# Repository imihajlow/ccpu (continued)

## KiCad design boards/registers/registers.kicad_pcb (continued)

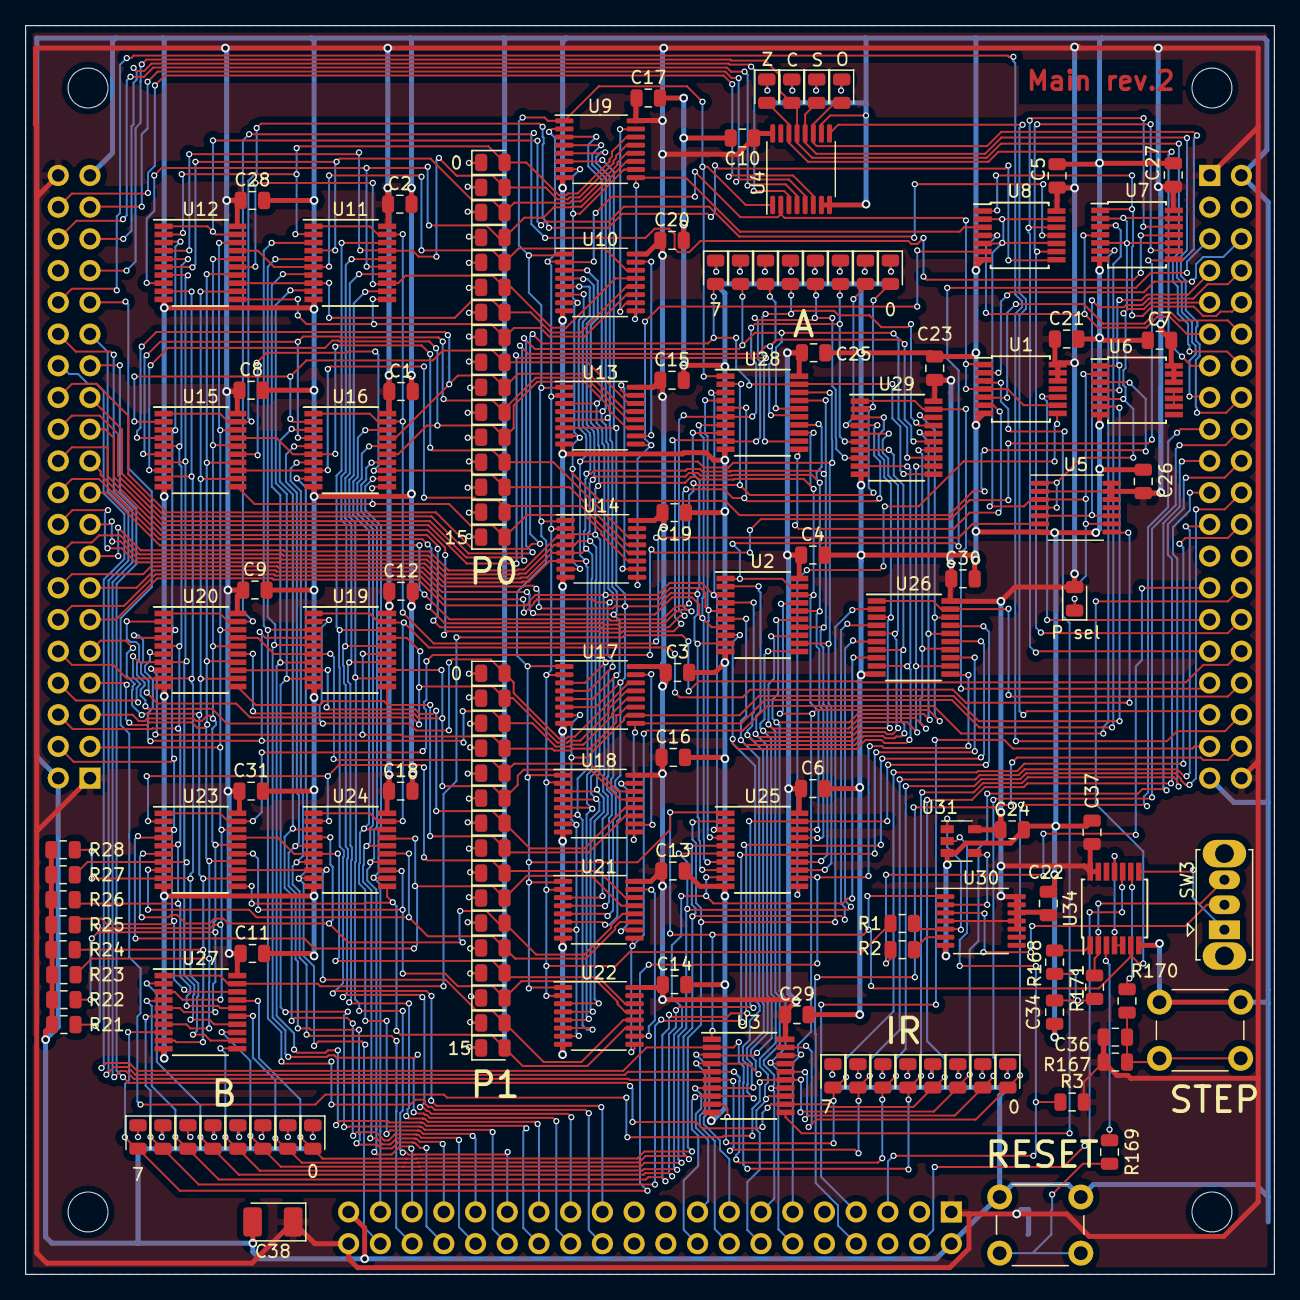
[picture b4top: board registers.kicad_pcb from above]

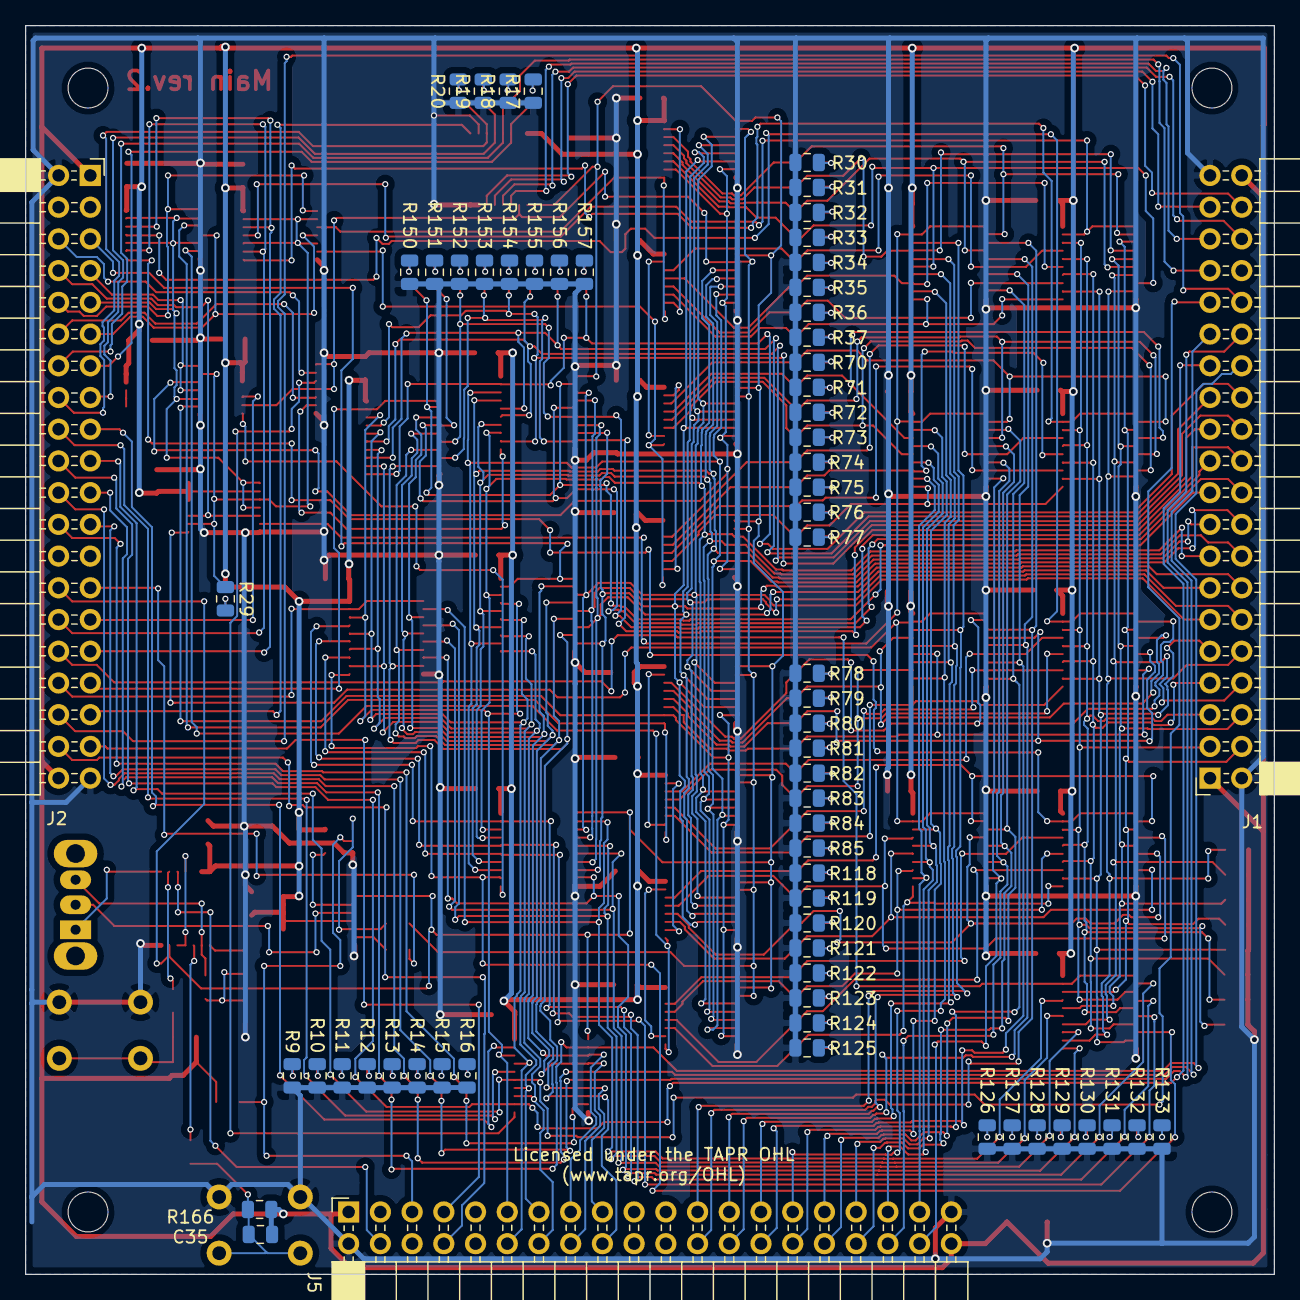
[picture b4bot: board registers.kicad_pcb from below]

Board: 2 copper layers, 100.0 x 100.0 mm, 217 parts (66 on the bottom side), 226 nets.

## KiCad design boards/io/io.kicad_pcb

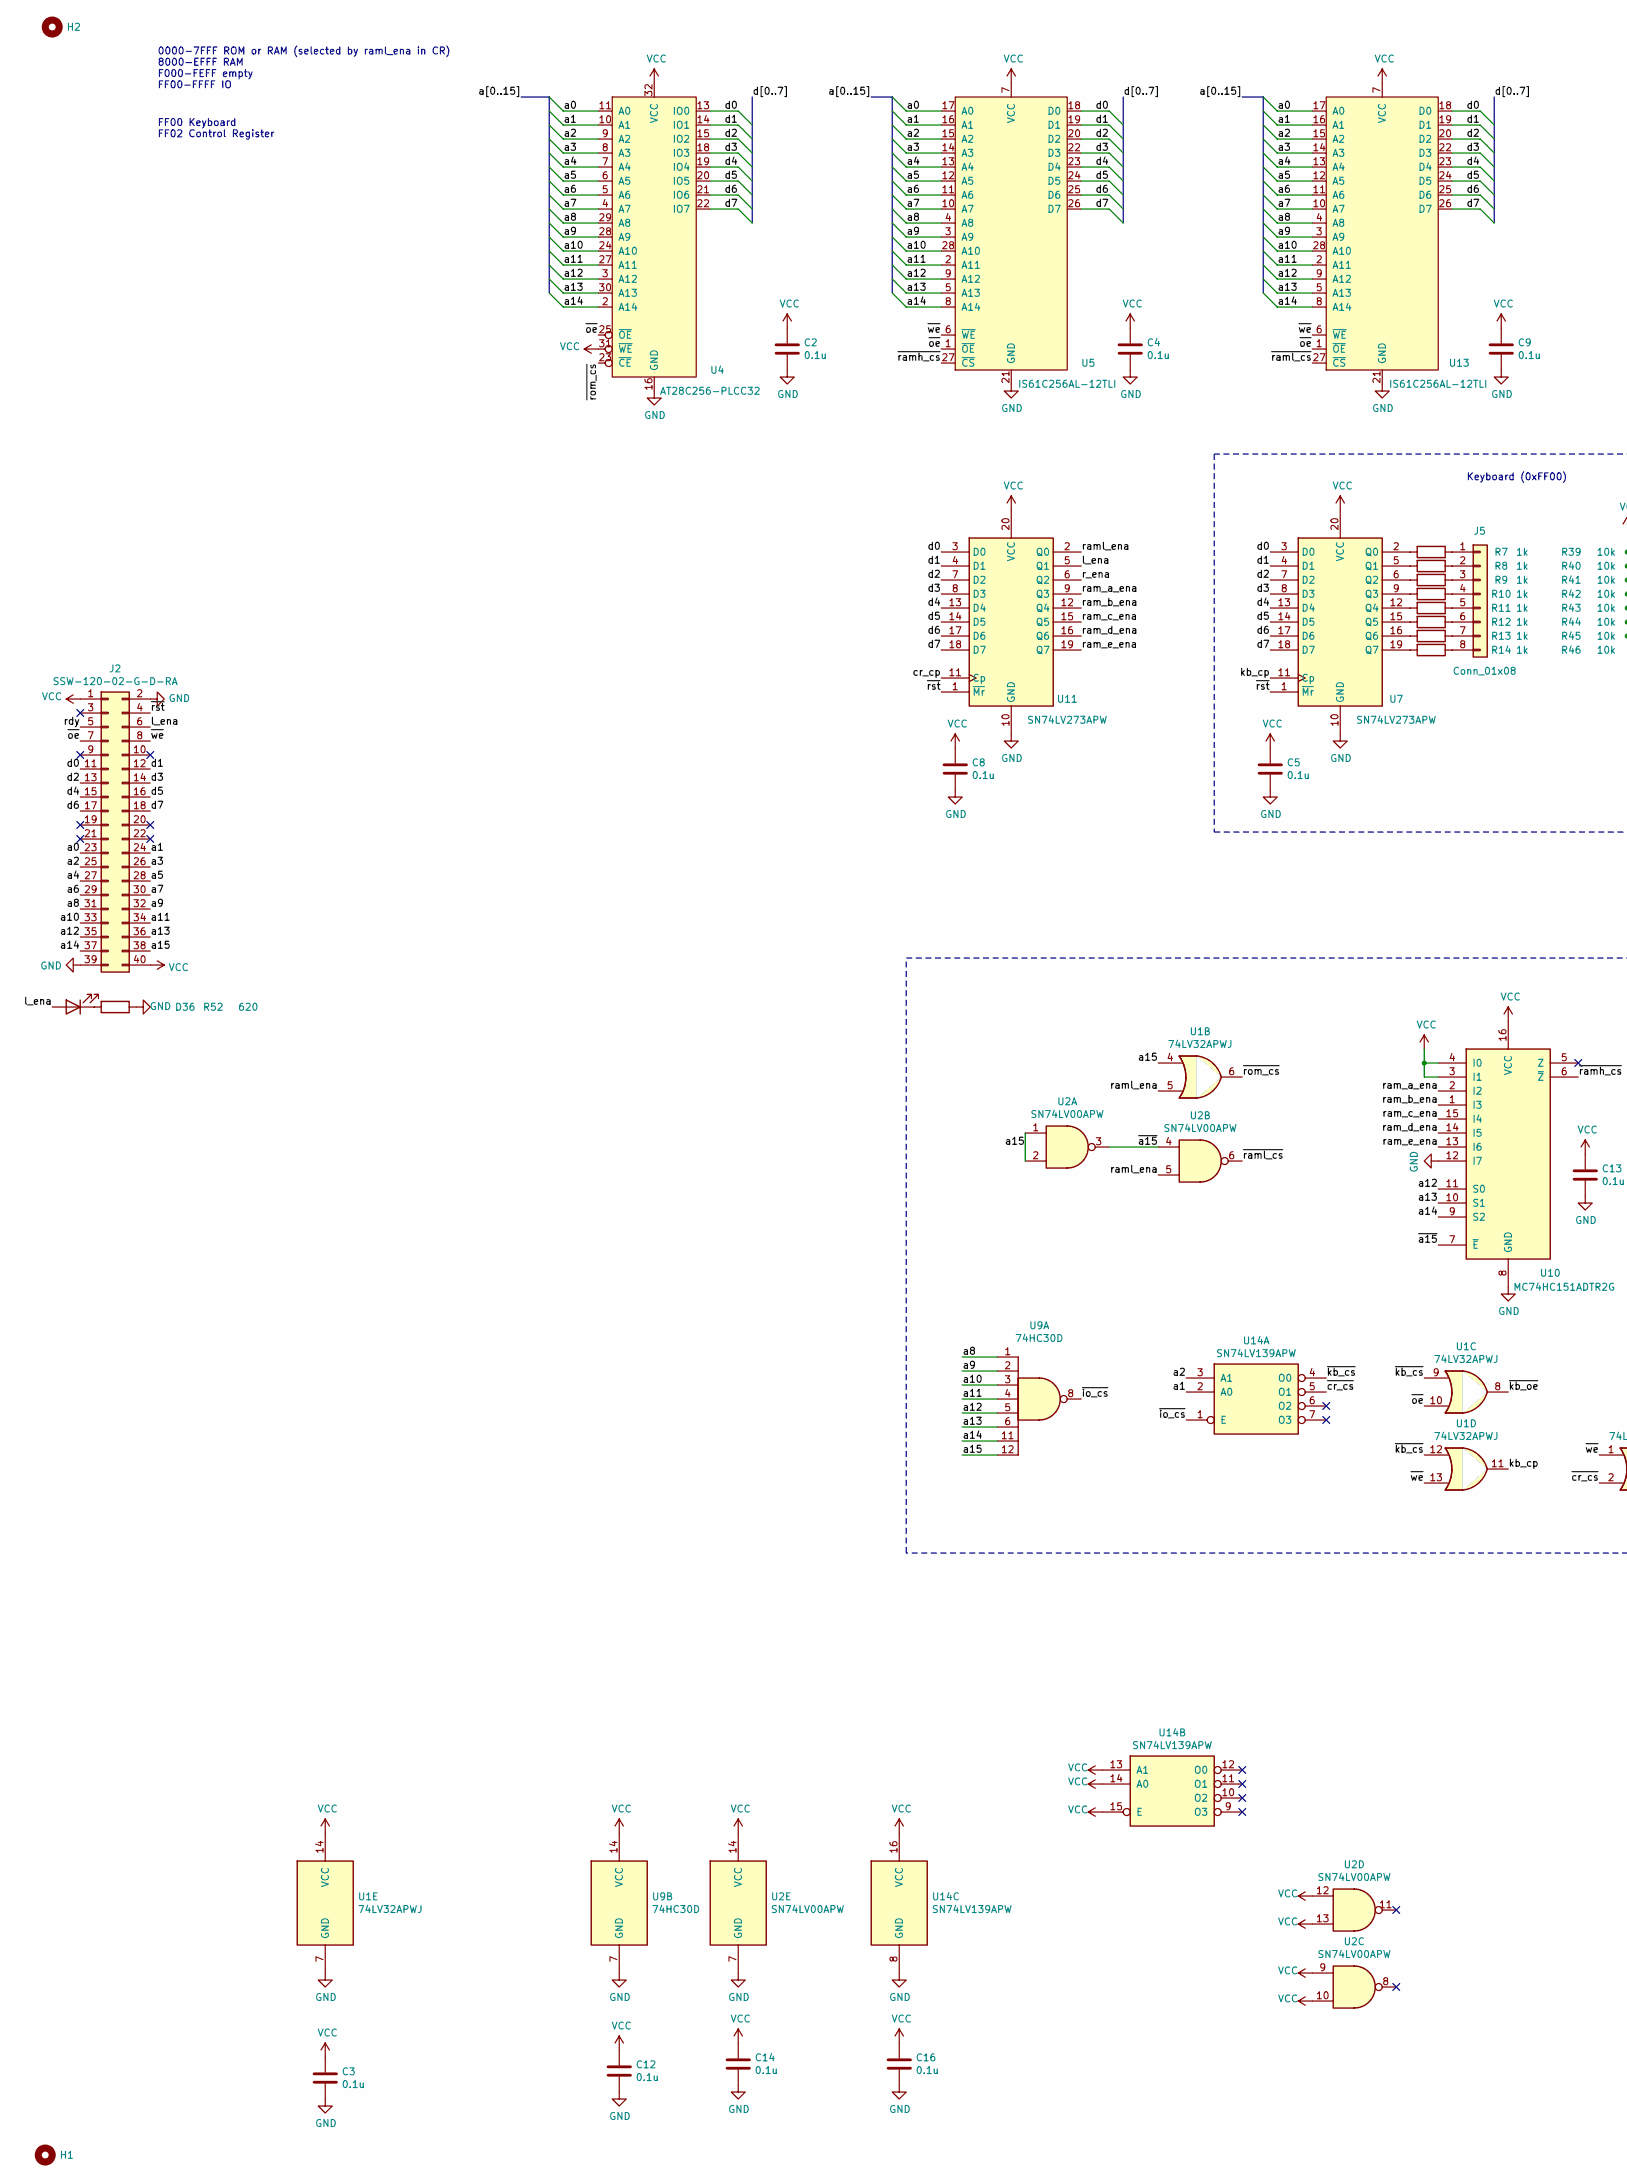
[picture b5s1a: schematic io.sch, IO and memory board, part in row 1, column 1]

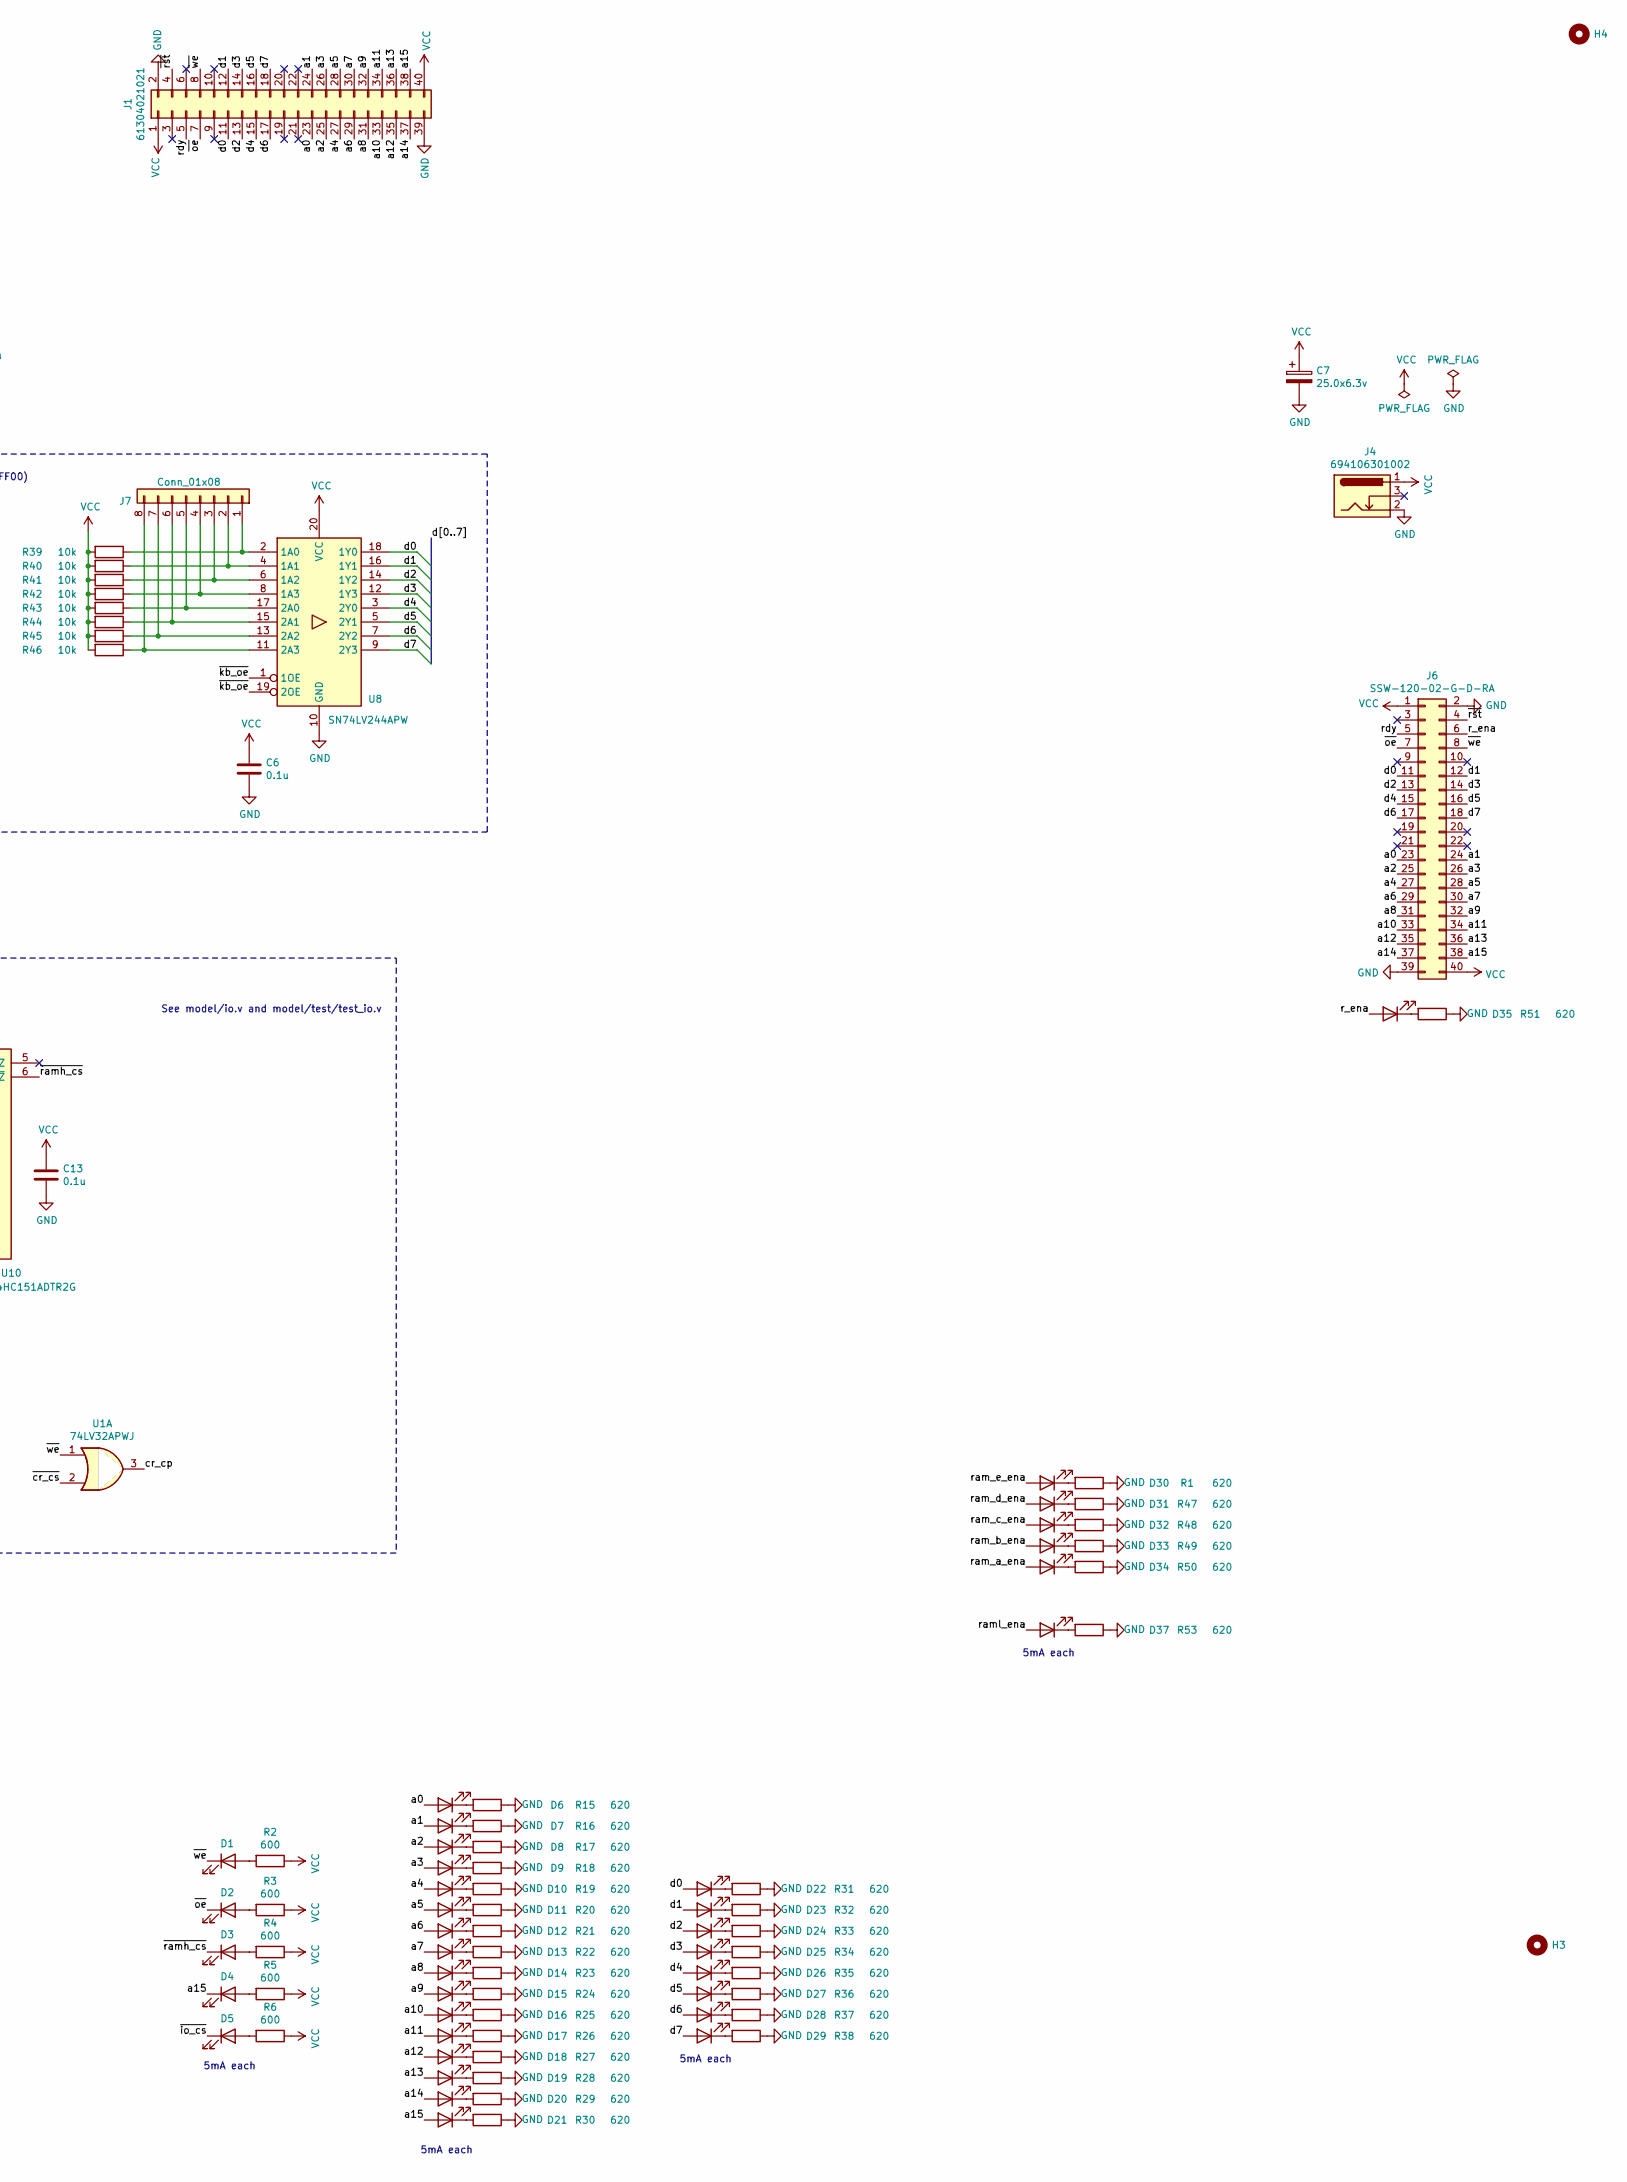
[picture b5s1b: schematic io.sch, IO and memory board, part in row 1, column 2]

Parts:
C2, C3, C4, C5, C6, C8, C9, C12, C13, C14, C16: 0.1u; C_0805_2012Metric
C7: 25.0x6.3v; CP_EIA-3528-21_Kemet-B_Pad1.50x2.35mm_HandSolder
D1, D2, D3, D4, D5: KP-2012CGCK; LED_0805_2012Metric
D6, D7, D8, D9, D10, D11, D12, D13, D14, D15, D16, D17, D18, D19, D20, D21, D22, D23, D24, D25, D26, D27, D28, D29, D30, D31, D32, D33, D34, D35, D36, D37: KP-2012EC; LED_0805_2012Metric
H1, H2, H3, H4: MountingHole; MountingHole_3.2mm_M3
J1: 61304021021; PinHeader_2x20_P2.54mm_Horizontal
J2, J6: SSW-120-02-G-D-RA; PinSocket_2x20_P2.54mm_Horizontal
J4: 694106301002; BarrelJack_Wuerth_6941xx301002
J5, J7: Conn_01x08; PinHeader_1x08_P2.54mm_Vertical
R1, R15, R16, R17, R18, R19, R20, R21, R22, R23, R24, R25, R26, R27, R28, R29, R30, R31, R32, R33, R34, R35, R36, R37, R38, R47, R48, R49, R50, R51, R52, R53: 620; R_0805_2012Metric
R2, R3, R4, R5, R6: 600; R_0805_2012Metric
R7, R8, R9, R10, R11, R12, R13, R14: 1k; R_0805_2012Metric
R39, R40, R41, R42, R43, R44, R45, R46: 10k; R_0805_2012Metric
U1: 74LV32APWJ; TSSOP-14_4.4x5mm_P0.65mm
U2: SN74LV00APW; TSSOP-14_4.4x5mm_P0.65mm
U4: AT28C256-PLCC32; PLCC-32_SMD_Socket
U5, U13: IS61C256AL-12TLI; TSOP-I-28_11.8x8mm_P0.55mm
U7, U11: SN74LV273APW; TSSOP-20_4.4x6.5mm_P0.65mm
U8: SN74LV244APW; TSSOP-20_4.4x6.5mm_P0.65mm
U9: 74HC30D; SOIC-14_3.9x8.7mm_P1.27mm
U10: MC74HC151ADTR2G; TSSOP-16_4.4x5mm_P0.65mm
U14: SN74LV139APW; TSSOP-16_4.4x5mm_P0.65mm

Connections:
/a0: D6.2 (A), J1.23, J2.23, J6.23, U4.11 (A0), U5.17 (A0), U13.17 (A0)
/a1: D7.2 (A), J1.24, J2.24, J6.24, U4.10 (A1), U5.16 (A1), U13.16 (A1), U14.2 (A0)
/a2: D8.2 (A), J1.25, J2.25, J6.25, U4.9 (A2), U5.15 (A2), U13.15 (A2), U14.3 (A1)
/a3: D9.2 (A), J1.26, J2.26, J6.26, U4.8 (A3), U5.14 (A3), U13.14 (A3)
/a4: D10.2 (A), J1.27, J2.27, J6.27, U4.7 (A4), U5.13 (A4), U13.13 (A4)
/a5: D11.2 (A), J1.28, J2.28, J6.28, U4.6 (A5), U5.12 (A5), U13.12 (A5)
/a6: D12.2 (A), J1.29, J2.29, J6.29, U4.5 (A6), U5.11 (A6), U13.11 (A6)
/a7: D13.2 (A), J1.30, J2.30, J6.30, U4.4 (A7), U5.10 (A7), U13.10 (A7)
/a8: D14.2 (A), J1.31, J2.31, J6.31, U4.29 (A8), U5.4 (A8), U9.1, U13.4 (A8)
/a9: D15.2 (A), J1.32, J2.32, J6.32, U4.28 (A9), U5.3 (A9), U9.2, U13.3 (A9)
/a10: D16.2 (A), J1.33, J2.33, J6.33, U4.24 (A10), U5.28 (A10), U9.3, U13.28 (A10)
/a11: D17.2 (A), J1.34, J2.34, J6.34, U4.27 (A11), U5.2 (A11), U9.4, U13.2 (A11)
/a12: D18.2 (A), J1.35, J2.35, J6.35, U4.3 (A12), U5.9 (A12), U9.5, U10.11 (S0), U13.9 (A12)
/a13: D19.2 (A), J1.36, J2.36, J6.36, U4.30 (A13), U5.5 (A13), U9.6, U10.10 (S1), U13.5 (A13)
/a14: D20.2 (A), J1.37, J2.37, J6.37, U4.2 (A14), U5.8 (A14), U9.11, U10.9 (S2), U13.8 (A14)
/a15: D4.1 (K), D21.2 (A), J1.38, J2.38, J6.38, U1.4, U2.1, U2.2, U9.12
/cr_cp: U1.3, U11.11 (Cp)
/d0: D22.2 (A), J1.11, J2.11, J6.11, U4.13 (IO0), U5.18 (D0), U7.3 (D0), U8.18 (1Y0), U11.3 (D0), U13.18 (D0)
/d1: D23.2 (A), J1.12, J2.12, J6.12, U4.14 (IO1), U5.19 (D1), U7.4 (D1), U8.16 (1Y1), U11.4 (D1), U13.19 (D1)
/d2: D24.2 (A), J1.13, J2.13, J6.13, U4.15 (IO2), U5.20 (D2), U7.7 (D2), U8.14 (1Y2), U11.7 (D2), U13.20 (D2)
/d3: D25.2 (A), J1.14, J2.14, J6.14, U4.18 (IO3), U5.22 (D3), U7.8 (D3), U8.12 (1Y3), U11.8 (D3), U13.22 (D3)
/d4: D26.2 (A), J1.15, J2.15, J6.15, U4.19 (IO4), U5.23 (D4), U7.13 (D4), U8.3 (2Y0), U11.13 (D4), U13.23 (D4)
/d5: D27.2 (A), J1.16, J2.16, J6.16, U4.20 (IO5), U5.24 (D5), U7.14 (D5), U8.5 (2Y1), U11.14 (D5), U13.24 (D5)
/d6: D28.2 (A), J1.17, J2.17, J6.17, U4.21 (IO6), U5.25 (D6), U7.17 (D6), U8.7 (2Y2), U11.17 (D6), U13.25 (D6)
/d7: D29.2 (A), J1.18, J2.18, J6.18, U4.22 (IO7), U5.26 (D7), U7.18 (D7), U8.9 (2Y3), U11.18 (D7), U13.26 (D7)
/kb_cp: U1.11, U7.11 (Cp)
/l_ena: D36.2 (A), J2.6, U11.5 (Q1)
/r_ena: D35.2 (A), J6.6, U11.6 (Q2)
/ram_a_ena: D34.2 (A), U10.2 (I2), U11.9 (Q3)
/ram_b_ena: D33.2 (A), U10.1 (I3), U11.12 (Q4)
/ram_c_ena: D32.2 (A), U10.15 (I4), U11.15 (Q5)
/ram_d_ena: D31.2 (A), U10.14 (I5), U11.16 (Q6)
/ram_e_ena: D30.2 (A), U10.13 (I6), U11.19 (Q7)
/raml_ena: D37.2 (A), U1.5, U2.5, U11.2 (Q0)
/rdy: J1.5, J2.5, J6.5
/~a15: U2.3, U2.4, U10.7 (~E)
/~cr_cs: U1.2, U14.5 (O1)
/~io_cs: D5.1 (K), U9.8, U14.1 (E)
/~kb_cs: U1.9, U1.12, U14.4 (O0)
/~kb_oe: U1.8, U8.1 (1OE), U8.19 (2OE)
/~oe: D2.1 (K), J1.7, J2.7, J6.7, U1.10, U4.25 (~OE), U5.1 (~OE), U13.1 (~OE)
/~ramh_cs: D3.1 (K), U5.27 (~CS), U10.6 (~Z)
/~raml_cs: U2.6, U13.27 (~CS)
/~rom_cs: U1.6, U4.23 (~CE)
/~rst: J1.4, J2.4, J6.4, U7.1 (~Mr), U11.1 (~Mr)
/~we: D1.1 (K), J1.8, J2.8, J6.8, U1.1, U1.13, U5.6 (~WE), U13.6 (~WE)
GND: C2.2, C3.2, C4.2, C5.2, C6.2, C7.2, C8.2, C9.2, C12.2, C13.2, C14.2, C16.2, J1.2, J1.39, J2.2, J2.39, J4.2, J6.2, J6.39, R1.1, R15.1, R16.1, R17.1, R18.1, R19.1, R20.1, R21.1, R22.1, R23.1, R24.1, R25.1, R26.1, R27.1, R28.1, R29.1, R30.1, R31.1, R32.1, R33.1, R34.1, R35.1, R36.1, R37.1, R38.1, R47.1, R48.1, R49.1, R50.1, R51.1, R52.1, R53.1, U1.7 (GND), U2.7 (GND), U4.16 (GND), U5.21 (GND), U7.10 (GND), U8.10 (GND), U9.7 (GND), U10.8 (GND), U10.12 (I7), U11.10 (GND), U13.21 (GND), U14.8 (GND)
unnamed: D1.2 (A), R2.2
unnamed: D2.2 (A), R3.2
unnamed: D3.2 (A), R4.2
unnamed: D4.2 (A), R5.2
unnamed: D5.2 (A), R6.2
unnamed: D6.1 (K), R15.2
unnamed: D7.1 (K), R16.2
unnamed: D8.1 (K), R17.2
unnamed: D9.1 (K), R18.2
unnamed: D10.1 (K), R19.2
unnamed: D11.1 (K), R20.2
unnamed: D12.1 (K), R21.2
unnamed: D13.1 (K), R22.2
unnamed: D14.1 (K), R23.2
unnamed: D15.1 (K), R24.2
unnamed: D16.1 (K), R25.2
unnamed: D17.1 (K), R26.2
unnamed: D18.1 (K), R27.2
unnamed: D19.1 (K), R28.2
unnamed: D20.1 (K), R29.2
unnamed: D21.1 (K), R30.2
unnamed: D22.1 (K), R31.2
unnamed: D23.1 (K), R32.2
unnamed: D24.1 (K), R33.2
unnamed: D25.1 (K), R34.2
unnamed: D26.1 (K), R35.2
unnamed: D27.1 (K), R36.2
unnamed: D28.1 (K), R37.2
unnamed: D29.1 (K), R38.2
unnamed: D30.1 (K), R1.2
unnamed: D31.1 (K), R47.2
unnamed: D32.1 (K), R48.2
unnamed: D33.1 (K), R49.2
unnamed: D34.1 (K), R50.2
unnamed: D35.1 (K), R51.2
unnamed: D36.1 (K), R52.2
unnamed: D37.1 (K), R53.2
unnamed: J5.1, R7.1
unnamed: J5.2, R8.1
unnamed: J5.3, R9.1
unnamed: J5.4, R10.1
unnamed: J5.5, R11.1
unnamed: J5.6, R12.1
unnamed: J5.7, R13.1
unnamed: J5.8, R14.1
unnamed: J7.1, R39.1, U8.2 (1A0)
unnamed: J7.2, R40.1, U8.4 (1A1)
unnamed: J7.3, R41.1, U8.6 (1A2)
unnamed: J7.4, R42.1, U8.8 (1A3)
unnamed: J7.5, R43.1, U8.17 (2A0)
unnamed: J7.6, R44.1, U8.15 (2A1)
unnamed: J7.7, R45.1, U8.13 (2A2)
unnamed: J7.8, R46.1, U8.11 (2A3)
unnamed: R7.2, U7.2 (Q0)
unnamed: R8.2, U7.5 (Q1)
unnamed: R9.2, U7.6 (Q2)
unnamed: R10.2, U7.9 (Q3)
unnamed: R11.2, U7.12 (Q4)
unnamed: R12.2, U7.15 (Q5)
unnamed: R13.2, U7.16 (Q6)
unnamed: R14.2, U7.19 (Q7)
VCC: C2.1, C3.1, C4.1, C5.1, C6.1, C7.1, C8.1, C9.1, C12.1, C13.1, C14.1, C16.1, J1.1, J1.40, J2.1, J2.40, J4.1, J6.1, J6.40, R2.1, R3.1, R4.1, R5.1, R6.1, R39.2, R40.2, R41.2, R42.2, R43.2, R44.2, R45.2, R46.2, U1.14 (VCC), U2.9, U2.10, U2.12, U2.13, U2.14 (VCC), U4.31 (~WE), U4.32 (VCC), U5.7 (VCC), U7.20 (VCC), U8.20 (VCC), U9.14 (VCC), U10.3 (I1), U10.4 (I0), U10.16 (VCC), U11.20 (VCC), U13.7 (VCC), U14.13 (A1), U14.14 (A0), U14.15 (E), U14.16 (VCC)

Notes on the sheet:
0000-7FFF ROM or RAM (selected by raml_ena in CR) 8000-EFFF RAM F000-FEFF empty FF00-FFFF IO
FF00 Keyboard FF02 Control Register
5mA each
See model/io.v and model/test/test_io.v
Keyboard (0xFF00)

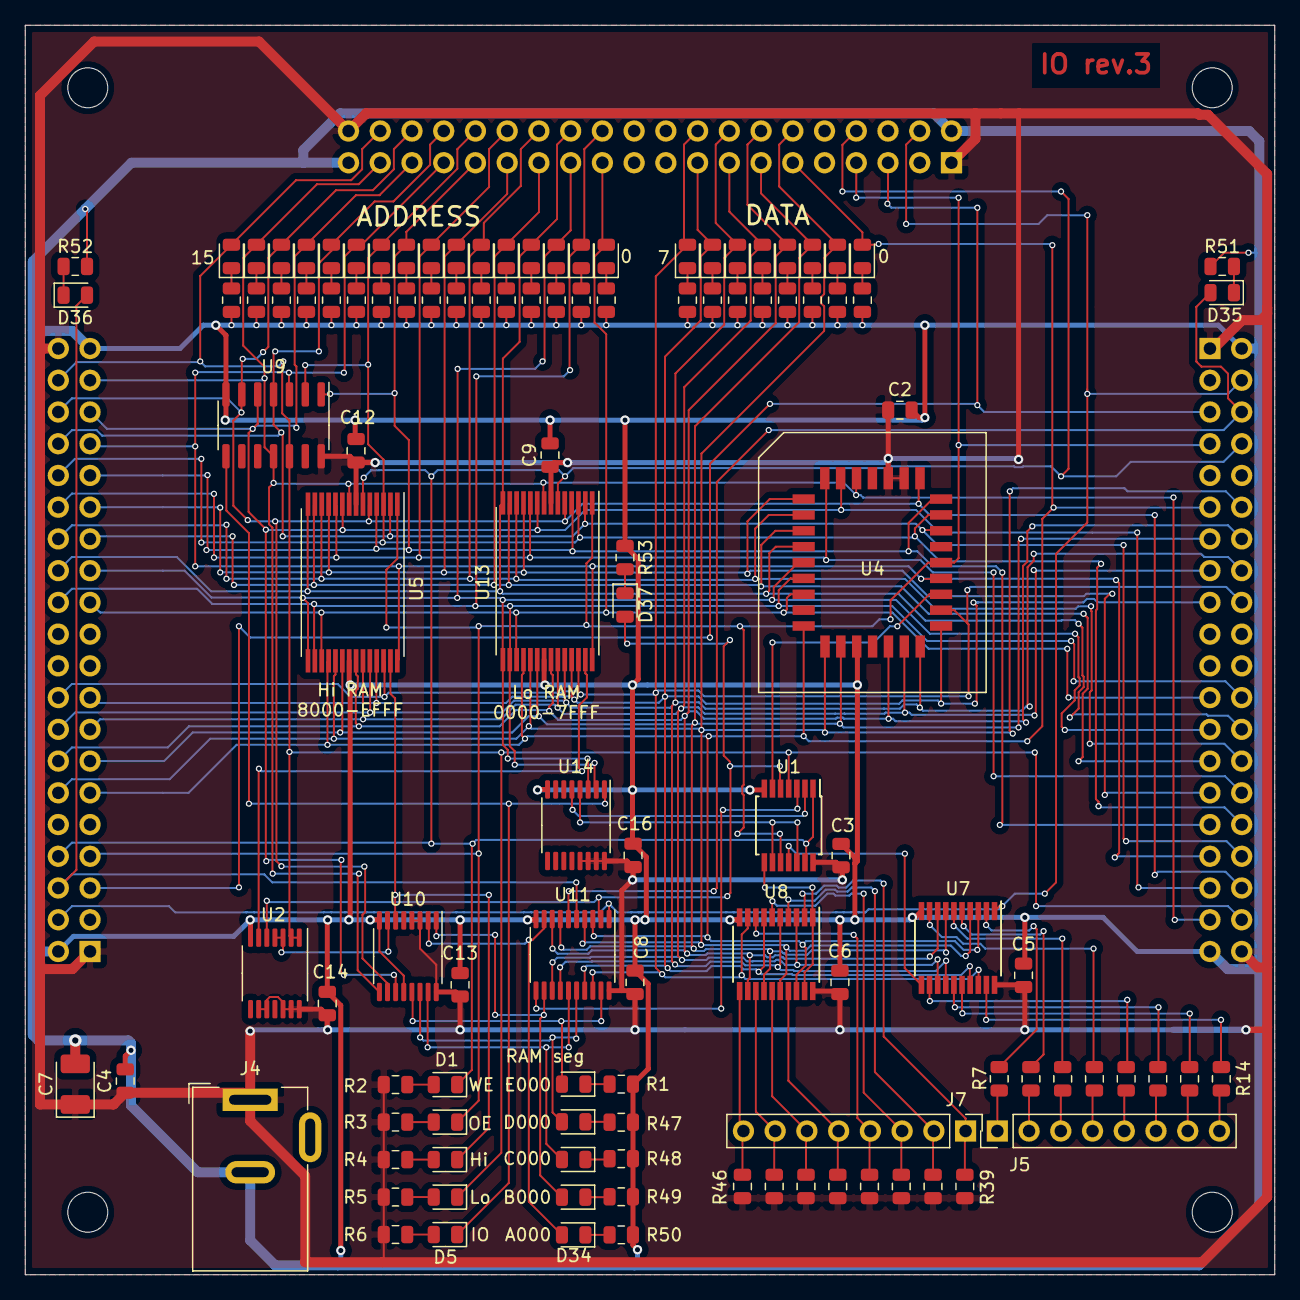
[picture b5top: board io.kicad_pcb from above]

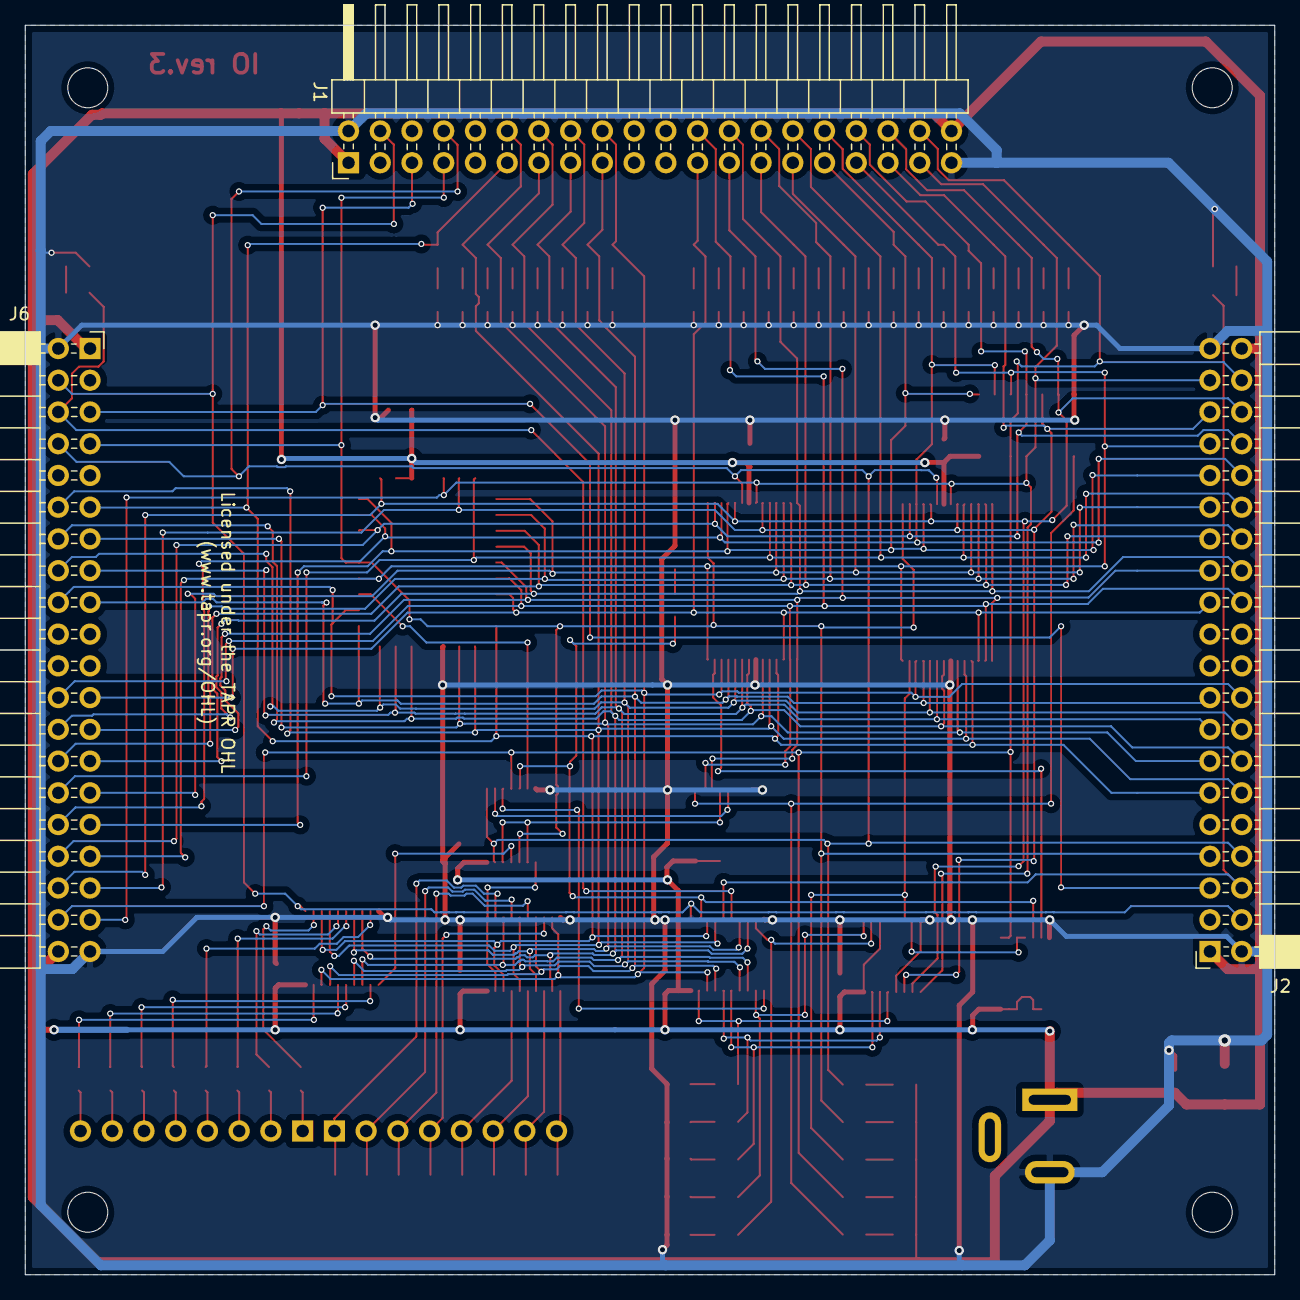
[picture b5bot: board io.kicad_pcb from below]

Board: 2 copper layers, 100.0 x 100.0 mm, 123 parts (3 on the bottom side), 109 nets.
